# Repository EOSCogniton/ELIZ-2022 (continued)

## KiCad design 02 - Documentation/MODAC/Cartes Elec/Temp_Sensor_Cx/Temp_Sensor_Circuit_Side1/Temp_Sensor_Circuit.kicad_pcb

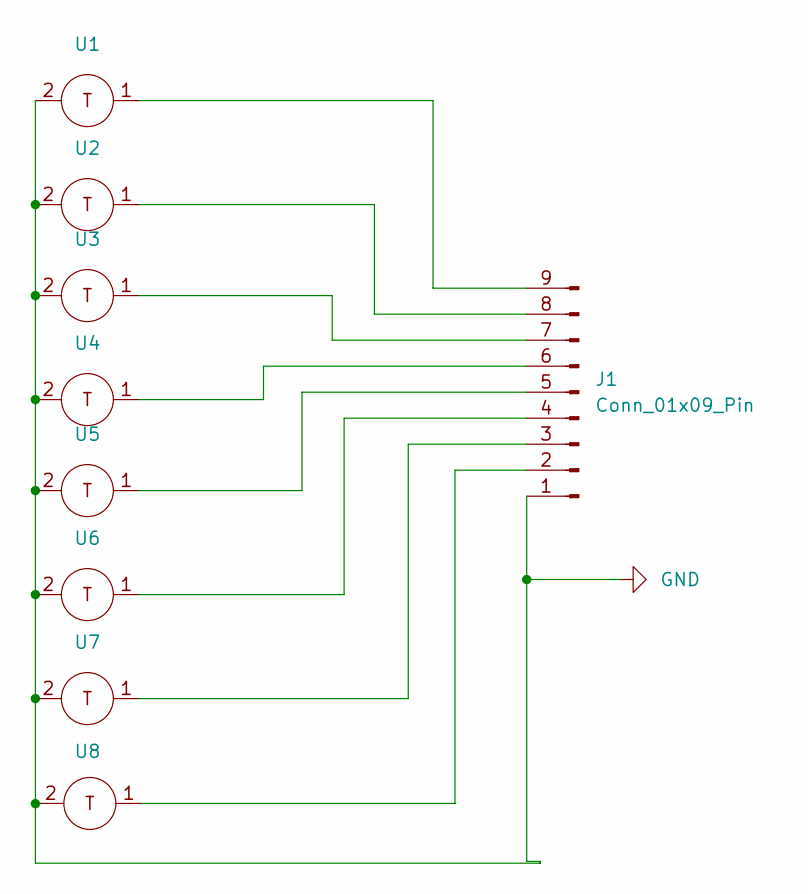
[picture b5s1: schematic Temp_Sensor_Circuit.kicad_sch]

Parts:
J1: Conn_01x09_Pin; PinHeader_1x09_P2.54mm_Vertical_SMD_Pin1Left
U1, U2, U3, U4, U5, U6, U7, U8: thermistor

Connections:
GND: J1.1, U1.2, U2.2, U3.2, U4.2, U5.2, U6.2, U7.2, U8.2
unnamed: J1.2, U8.1
unnamed: J1.3, U7.1
unnamed: J1.4, U6.1
unnamed: J1.5, U5.1
unnamed: J1.6, U4.1
unnamed: J1.7, U3.1
unnamed: J1.8, U2.1
unnamed: J1.9, U1.1

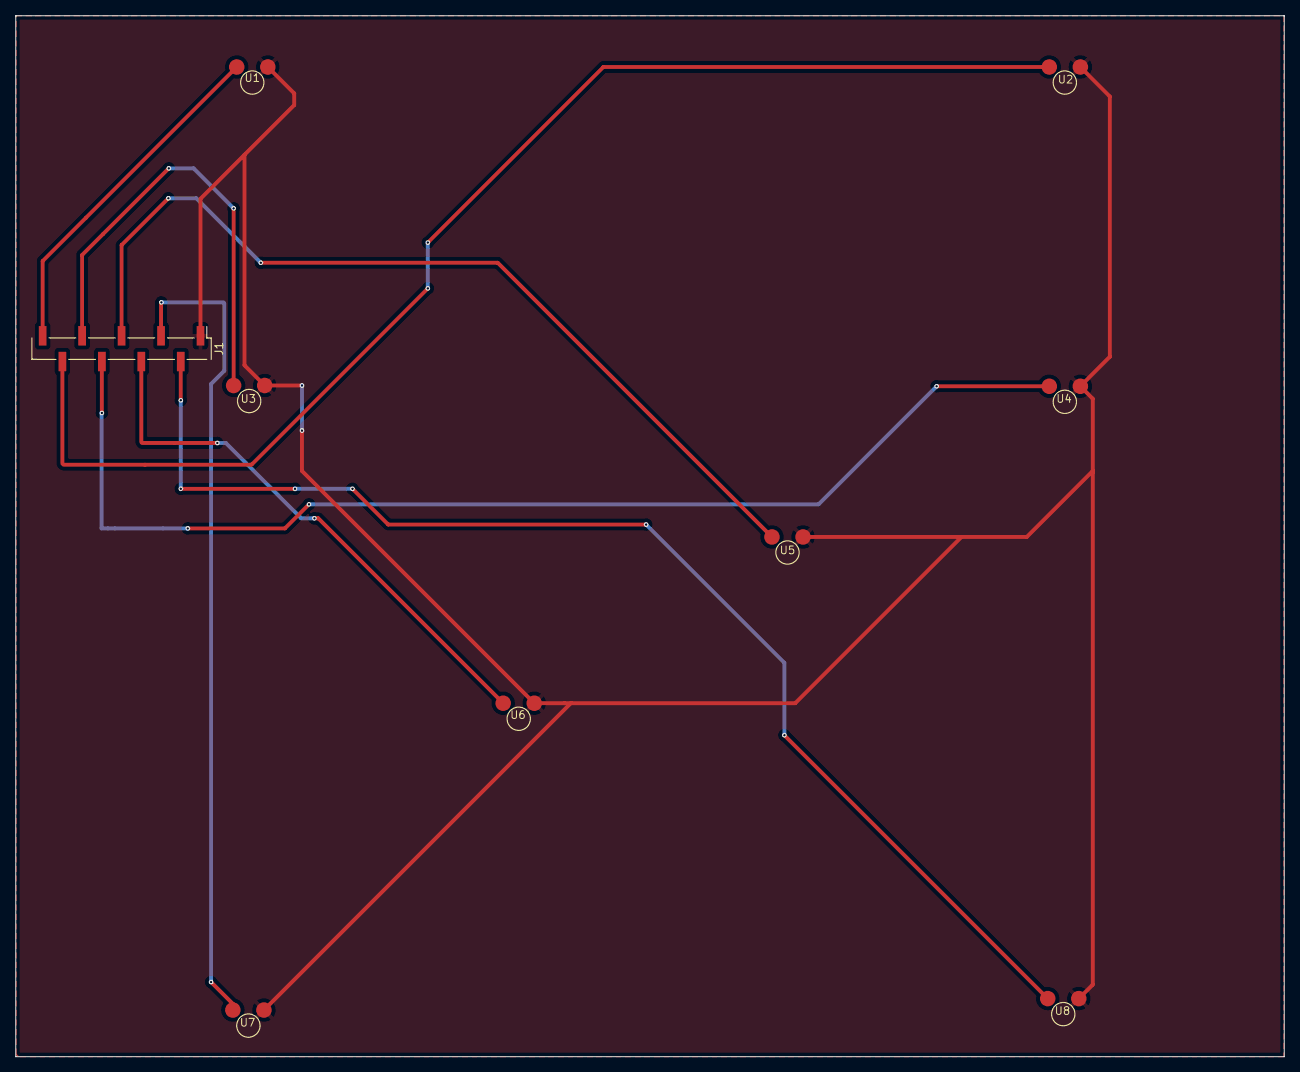
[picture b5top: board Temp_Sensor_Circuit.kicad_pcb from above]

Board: 2 copper layers, 163.3 x 134.0 mm, 9 parts (0 on the bottom side), 9 nets.

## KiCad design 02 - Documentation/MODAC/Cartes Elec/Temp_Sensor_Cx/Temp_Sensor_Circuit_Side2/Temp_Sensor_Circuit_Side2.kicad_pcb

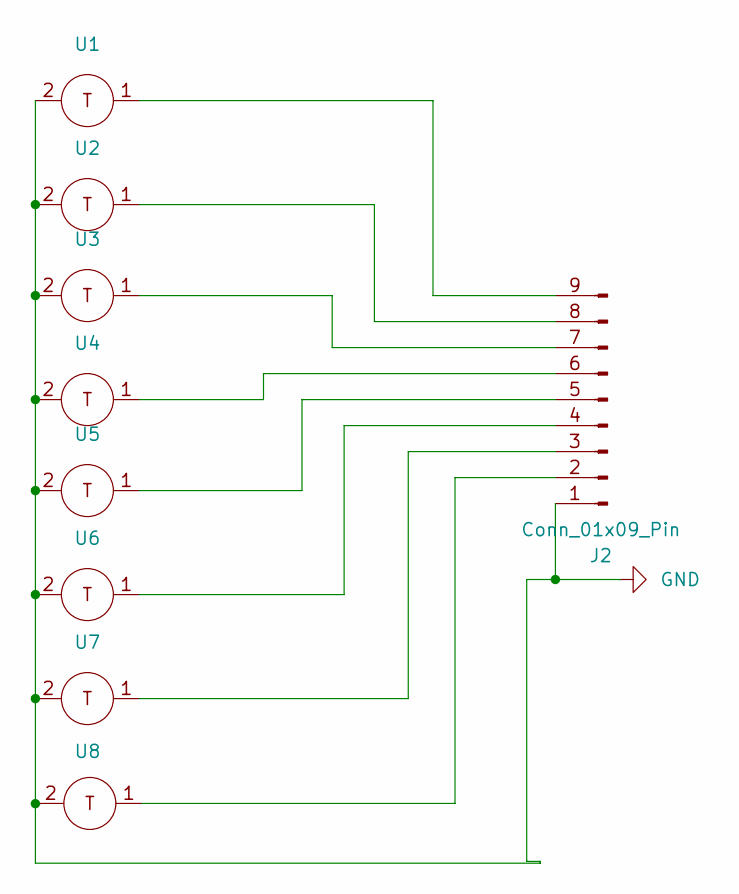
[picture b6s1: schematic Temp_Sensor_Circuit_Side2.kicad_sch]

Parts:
J2: Conn_01x09_Pin; PinHeader_1x09_P2.54mm_Vertical_SMD_Pin1Left
U1, U2, U3, U4, U5, U6, U7, U8: therm

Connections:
GND: J2.1, U1.2, U2.2, U3.2, U4.2, U5.2, U6.2, U7.2, U8.2
unnamed: J2.2, U8.1
unnamed: J2.3, U7.1
unnamed: J2.4, U6.1
unnamed: J2.5, U5.1
unnamed: J2.6, U4.1
unnamed: J2.7, U3.1
unnamed: J2.8, U2.1
unnamed: J2.9, U1.1

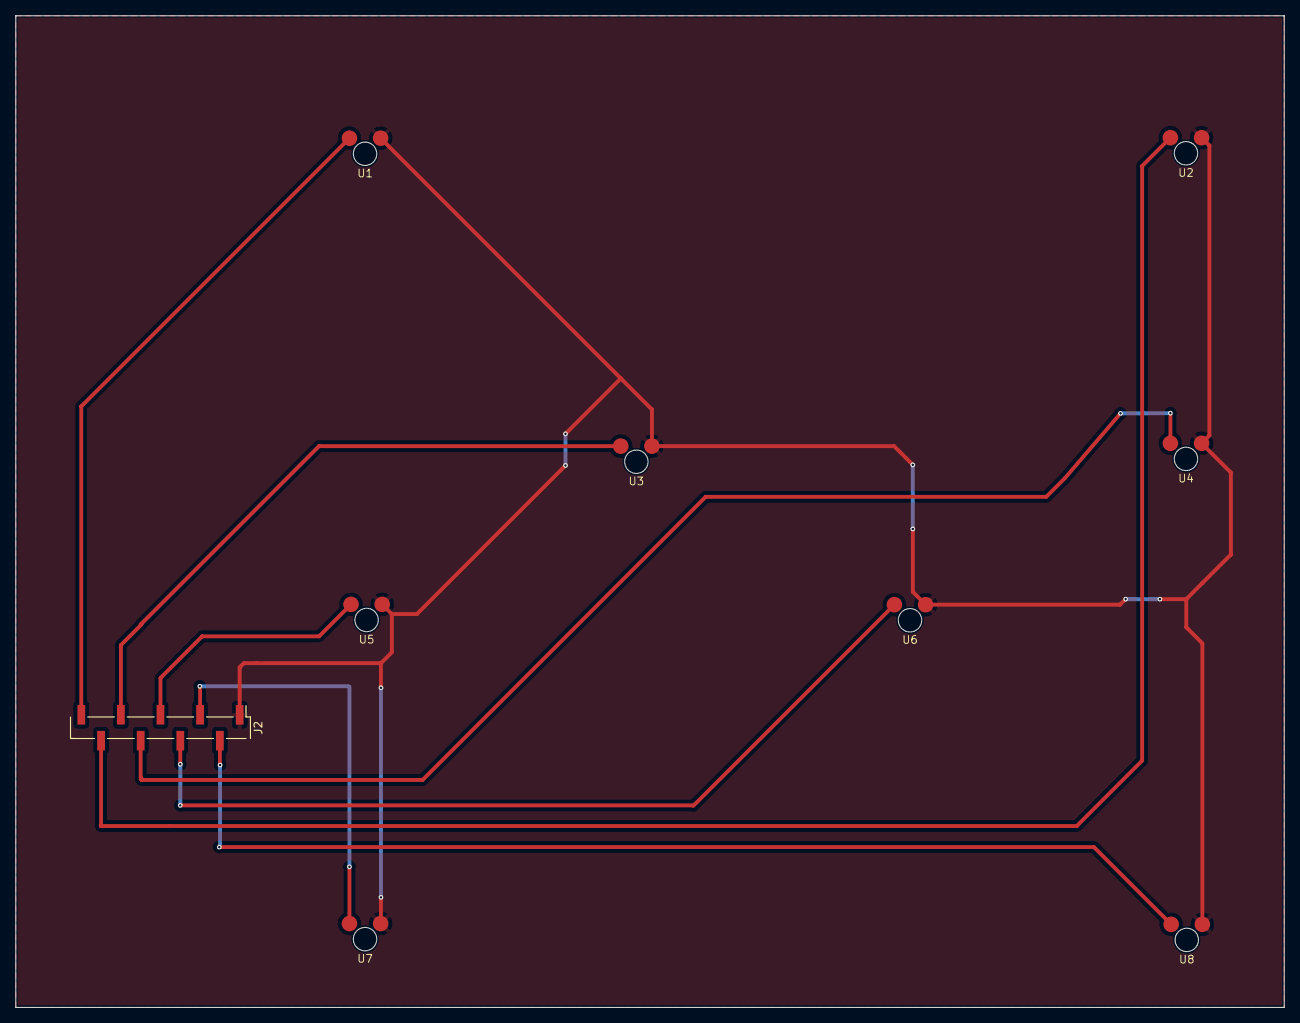
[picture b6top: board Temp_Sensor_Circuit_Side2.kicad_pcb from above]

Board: 2 copper layers, 162.7 x 127.2 mm, 9 parts (0 on the bottom side), 9 nets.

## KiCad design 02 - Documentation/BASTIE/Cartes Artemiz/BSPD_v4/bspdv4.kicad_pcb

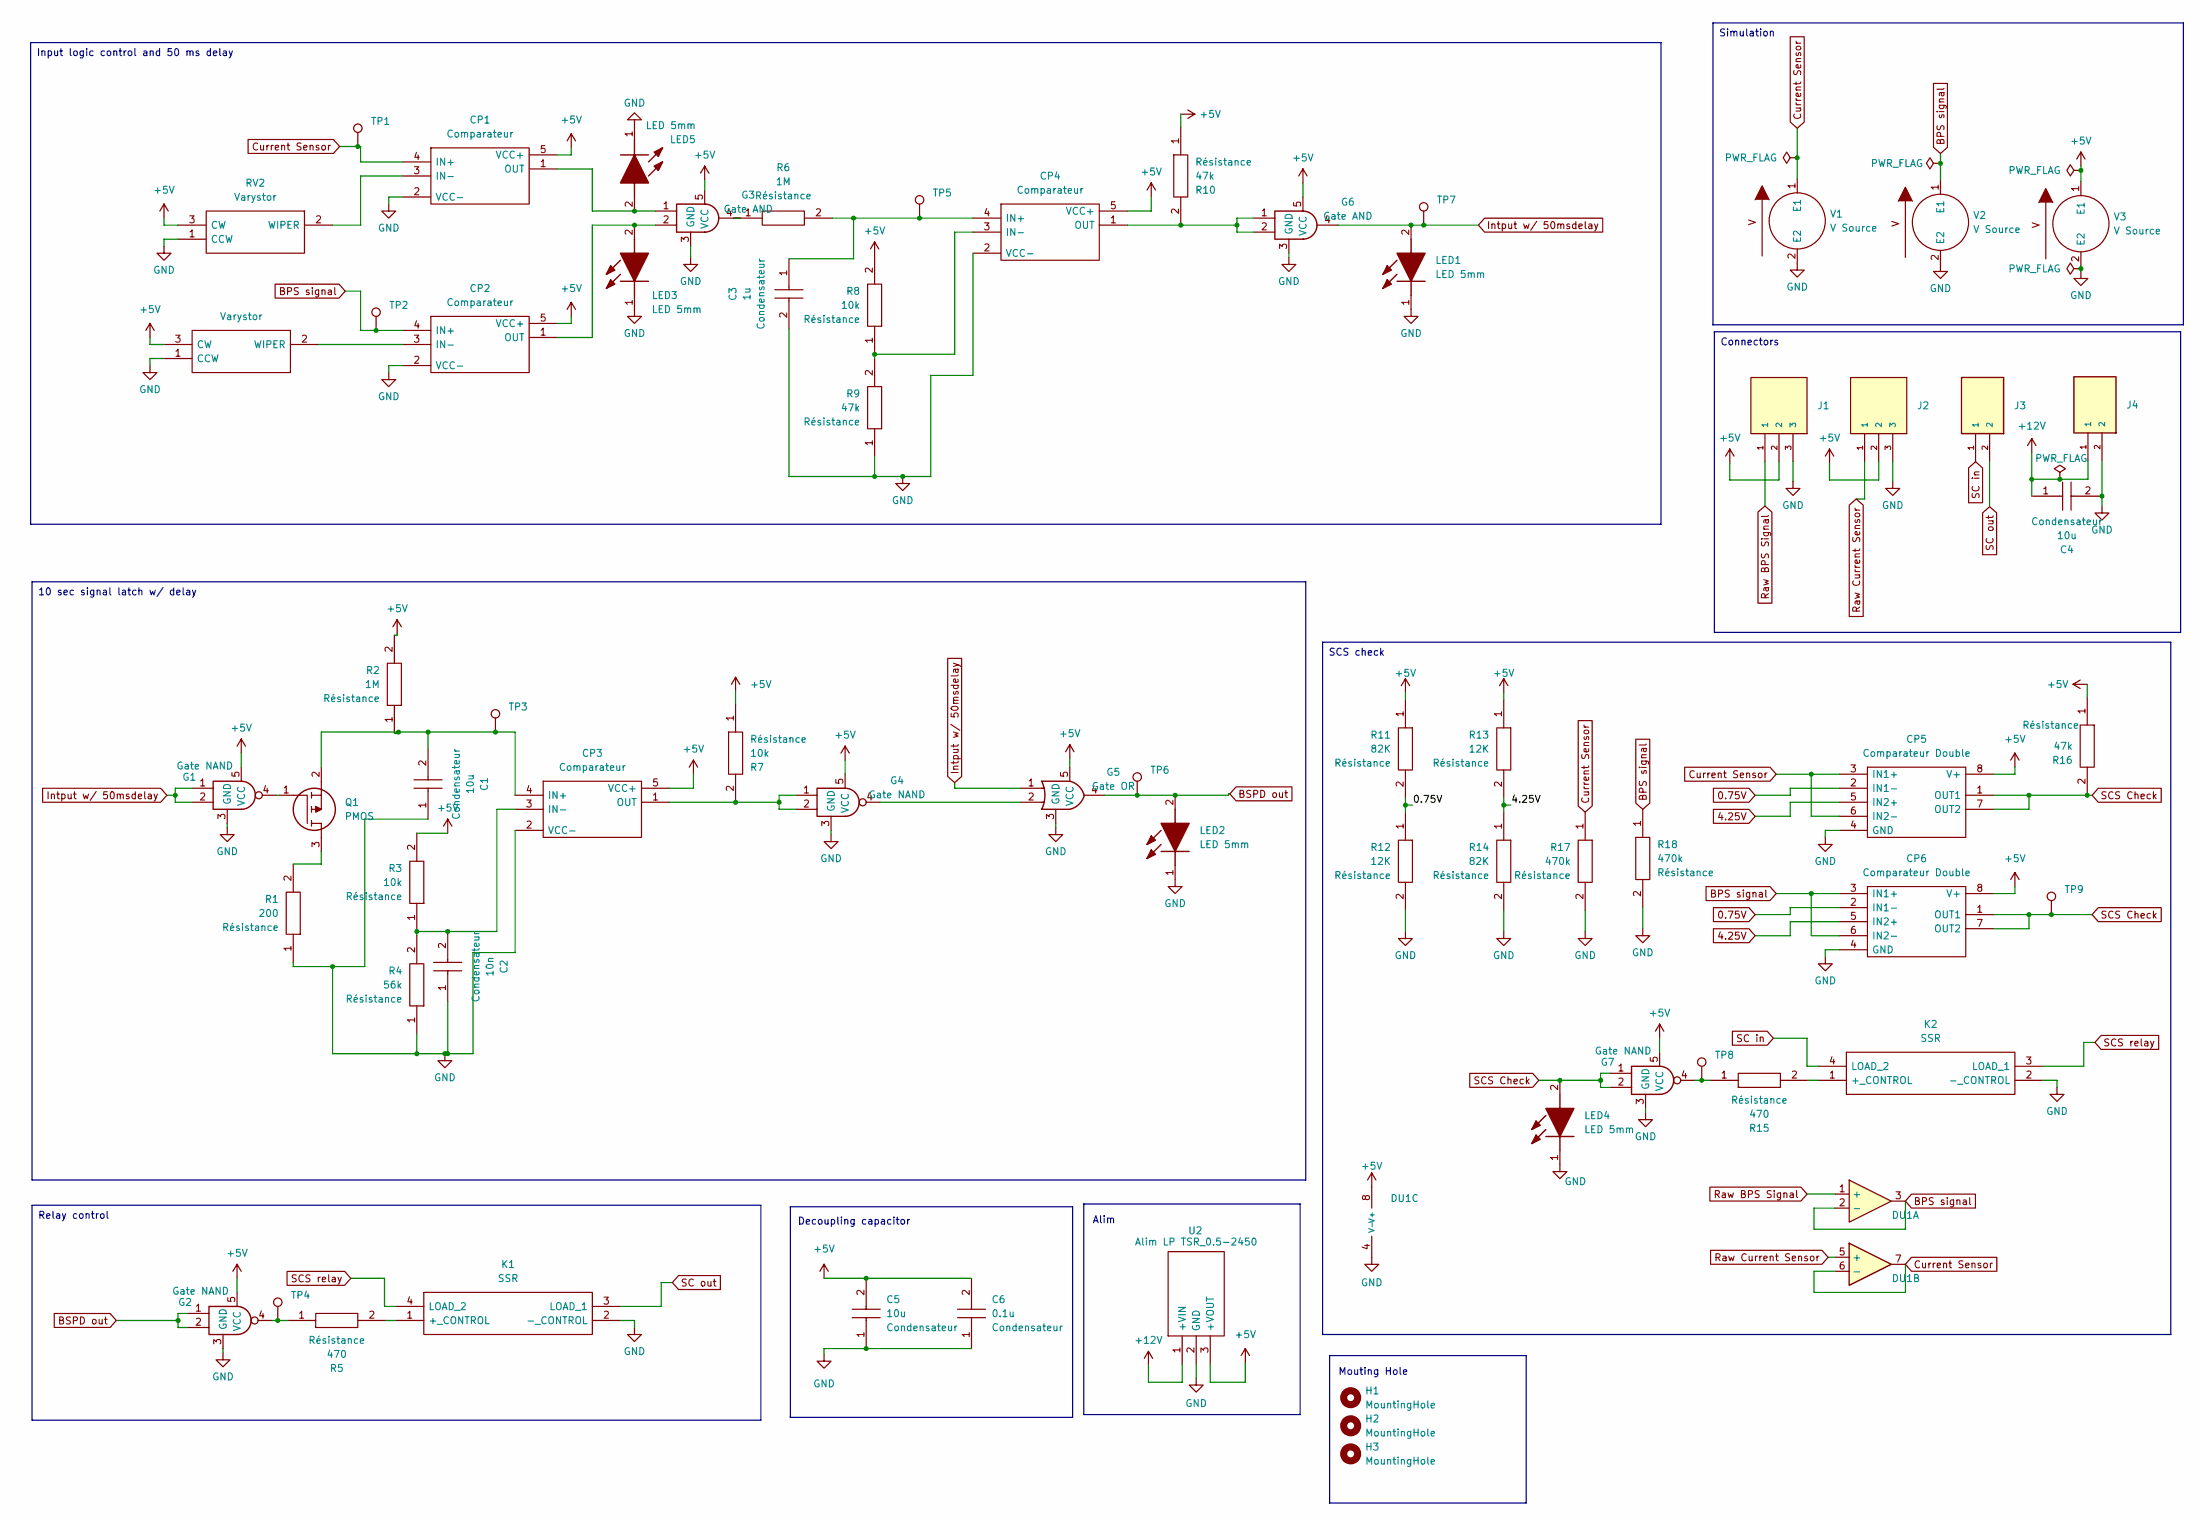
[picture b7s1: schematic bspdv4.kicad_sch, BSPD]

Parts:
C1, C4, C5: 10u; CP_Radial_D5.0mm_P2.00mm; Manufacturer_Part_Number 0805Y1000104JXT
C2: 10n; CAPC2012X130N; Manufacturer_Part_Number 0805Y1000104JXT
C3: 1u; CAPC2012X130N; Manufacturer_Part_Number 0805Y1000104JXT
C6: 0.1u; CAPC2012X130N; Manufacturer_Part_Number 0805Y1000104JXT
CP1, CP2, CP3, CP4: Comparateur TS391ILT; SOT95P280X145-5N; Manufacturer_Part_Number TS391ILT; Mouser Part Number 511-TS391IL
CP5, CP6: Comparateur Double LM393LVDR; SOIC127P600X175-8N; Manufacturer_Part_Number LM393LVDR; Mouser Part Number 595-LM393LVDR
DU1: Opamp_Dual; TSSOP-8_4.4x3mm_P0.65mm; Manufacturer_Part_Number TLV9062QPWRQ1; Mouser Part Number 595-TLV9062QPWRQ1
G1, G2, G4, G7: Gate NAND SN74AHCT1G00DBVR; SOT95P280X145-5N; Manufacturer_Part_Number SN74AHCT1G00DBVR; Mouser Part Number 595-SN74AHCT1G00DBVR
G3, G6: Gate AND SN74AHCT1G08DBVR; SOT95P280X145-5N; Manufacturer_Part_Number SN74AHCT1G08DBVR; Mouser Part Number 595-SN74AHCT1G08DBVR
G5: Gate OR SN74AHCT1G32DBVR; SOT95P280X145-5N; Manufacturer_Part_Number SN74AHCT1G32DBVR; Mouser Part Number 595-SN74AHCT1G32DBVR
H1, H2, H3: MountingHole; MountingHole_2.7mm_M2.5
J1, J2: 3P Droit 22-11-2032; MOLEX_22-11-2032; Manufacturer_Part_Number 22-11-2032; Mouser Part Number 538-22-11-2032
J3, J4: 2P Droit 2-11-2022; MOLEX_22-11-2022; Manufacturer_Part_Number 22-11-2022; Mouser Part Number 538-22-11-2022
K1, K2: SSR CPC1394GR; CPC1394GR; Manufacturer_Part_Number CPC1394GR; Mouser Part Number 849-CPC1394GR
LED1, LED2, LED3, LED4, LED5: LED 5mm; 4302H55V; Mouser Part Number 606-4302H5-5V
Q1: PMOS SI2343CDS-T1-GE3; SOT95P237X112-3N; Manufacturer_Part_Number SI2343CDS-T1-GE3; Mouser Part Number 781-SI2343CDS-T1-GE3
R1: 200; RESC3216X70N; Manufacturer_Part_Number RK73H2BLTDD2152F; Mouser Part Number N/A
R2, R6: 1M; RESC3216X70N; Manufacturer_Part_Number RK73H2BLTDD2152F; Mouser Part Number N/A
R3, R7, R8: 10k; RESC3216X70N; Manufacturer_Part_Number RK73H2BLTDD2152F; Mouser Part Number N/A
R4: 56k; RESC3216X70N; Manufacturer_Part_Number RK73H2BLTDD2152F; Mouser Part Number N/A
R5, R15: 470; RESC3216X70N; Manufacturer_Part_Number RK73H2BLTDD2152F; Mouser Part Number N/A
R9, R10, R16: 47k; RESC3216X70N; Manufacturer_Part_Number RK73H2BLTDD2152F; Mouser Part Number N/A
R11, R14: 82K; RESC3216X70N; Manufacturer_Part_Number RK73H2BLTDD2152F; Mouser Part Number N/A
R12, R13: 12K; RESC3216X70N; Manufacturer_Part_Number RK73H2BLTDD2152F; Mouser Part Number N/A
R17, R18: 470k; RESC3216X70N; Manufacturer_Part_Number RK73H2BLTDD2152F; Mouser Part Number N/A
RV1, RV2: Varystor 3296Y-1-223LF; 3296Y1223LF; Manufacturer_Part_Number 3296Y-1-223LF; Mouser Part Number 652-3296Y-1-223LF
TP1, TP2, TP3, TP4, TP5, TP6, TP7, TP8, TP9: type="R" model="TestPoint" lib=""; TestPoint_Pad_D2.0mm
U2: Alim LP TSR_0.5-2450; TSR-0.5-2433; Manufacturer_Part_Number TSR 0.5-2450; Mouser Part Number 495-TSR0.5-2450
V1, V2, V3: 5

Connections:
0.75V: CP5.2 (IN1-), CP6.2 (IN1-), R11.2, R12.1
4.25V: CP5.5 (IN2+), CP6.5 (IN2+), R13.2, R14.1
+5V: C5.2, C6.2, CP1.5 (VCC+), CP2.5 (VCC+), CP3.5 (VCC+), CP4.5 (VCC+), CP5.8 (V+), CP6.8 (V+), DU1.8 (V+), G1.5 (VCC), G2.5 (VCC), G3.5 (VCC), G4.5 (VCC), G5.5 (VCC), G6.5 (VCC), G7.5 (VCC), J1.2, J2.2, R2.2, R3.2, R7.1, R8.2, R10.1, R11.1, R13.1, R16.1, RV1.3 (CW), RV2.3 (CW), U2.3 (+VOUT), V3.1 (E1)
+12V: C4.1, J4.1, U2.1 (+VIN)
BPS signal: CP2.4 (IN+), CP6.3 (IN1+), CP6.6 (IN2-), DU1.2 (-), DU1.3, R18.1, TP2.1, V2.1 (E1)
BSPD out: G2.1, G2.2, G5.4, LED2.2 (A), TP6.1
Current Sensor: CP1.4 (IN+), CP5.3 (IN1+), CP5.6 (IN2-), DU1.6 (-), DU1.7, R17.1, TP1.1, V1.1 (E1)
GND: C1.1, C2.1, C3.2, C4.2, C5.1, C6.1, CP1.2 (VCC-), CP2.2 (VCC-), CP3.2 (VCC-), CP4.2 (VCC-), CP5.4 (GND), CP6.4 (GND), DU1.4 (V-), G1.3 (GND), G2.3 (GND), G3.3 (GND), G4.3 (GND), G5.3 (GND), G6.3 (GND), G7.3 (GND), J1.3, J2.3, J4.2, K1.2 (-_CONTROL), K2.2 (-_CONTROL), LED1.1 (K), LED2.1 (K), LED3.1 (K), LED4.1 (K), LED5.1 (K), R1.1, R4.1, R9.1, R12.2, R14.2, R17.2, R18.2, RV1.1 (CCW), RV2.1 (CCW), U2.2 (GND), V1.2 (E2), V2.2 (E2), V3.2 (E2)
Intput w/ 50msdelay: G1.1, G1.2, G5.1, G6.4, LED1.2 (A), TP7.1
unnamed: CP1.3 (IN-), RV2.2 (WIPER)
unnamed: CP1.1 (OUT), G3.1, LED5.2 (A)
unnamed: CP2.3 (IN-), RV1.2 (WIPER)
unnamed: CP2.1 (OUT), G3.2, LED3.2 (A)
unnamed: C1.2, CP3.4 (IN+), Q1.2, R2.1, TP3.1
unnamed: C2.2, CP3.3 (IN-), R3.1, R4.2
unnamed: CP3.1 (OUT), G4.1, G4.2, R7.2
unnamed: C3.1, CP4.4 (IN+), R6.2, TP5.1
unnamed: CP4.3 (IN-), R8.1, R9.2
unnamed: CP4.1 (OUT), G6.1, G6.2, R10.2
unnamed: G1.4, Q1.1
unnamed: G2.4, R5.1, TP4.1
unnamed: G3.4, R6.1
unnamed: G4.4, G5.2
unnamed: G7.4, R15.1, TP8.1
unnamed: K1.1 (+_CONTROL), R5.2
unnamed: K2.1 (+_CONTROL), R15.2
unnamed: Q1.3, R1.2
Raw BPS Signal: DU1.1 (+), J1.1
Raw Current Sensor: DU1.5 (+), J2.1
SC in: J3.1, K2.4 (LOAD_2)
SC out: J3.2, K1.3 (LOAD_1)
SCS Check: CP5.1 (OUT1), CP5.7 (OUT2), CP6.1 (OUT1), CP6.7 (OUT2), G7.1, G7.2, LED4.2 (A), R16.2, TP9.1
SCS relay: K1.4 (LOAD_2), K2.3 (LOAD_1)

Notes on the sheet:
Relay control
10 sec signal latch w/ delay
Connectors
SCS check
Simulation
Input logic control and 50 ms delay
Alim
Mouting Hole
Decoupling capacitor

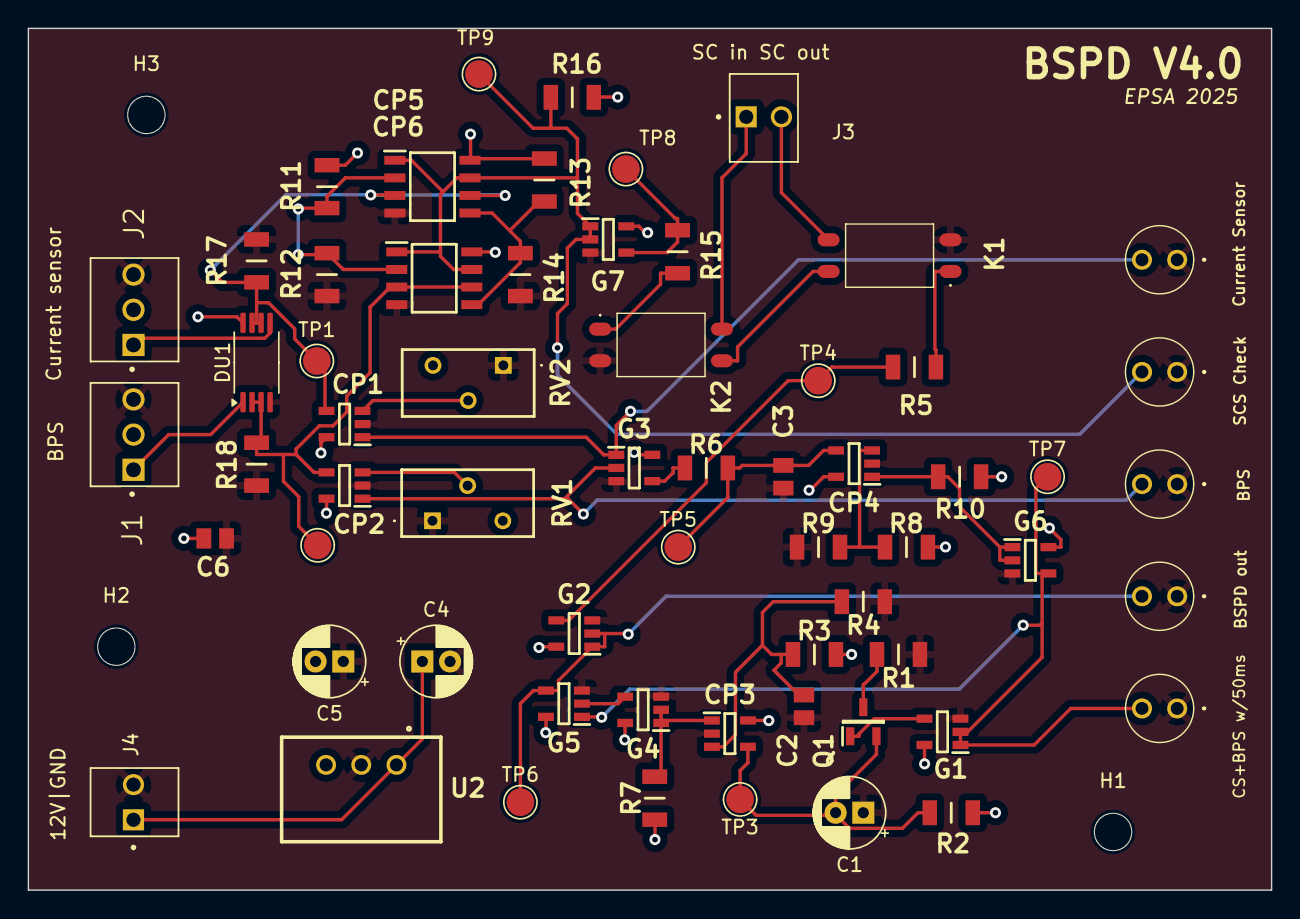
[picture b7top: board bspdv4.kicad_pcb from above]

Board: 2 copper layers, 89.8 x 62.2 mm, 65 parts (0 on the bottom side), 33 nets.

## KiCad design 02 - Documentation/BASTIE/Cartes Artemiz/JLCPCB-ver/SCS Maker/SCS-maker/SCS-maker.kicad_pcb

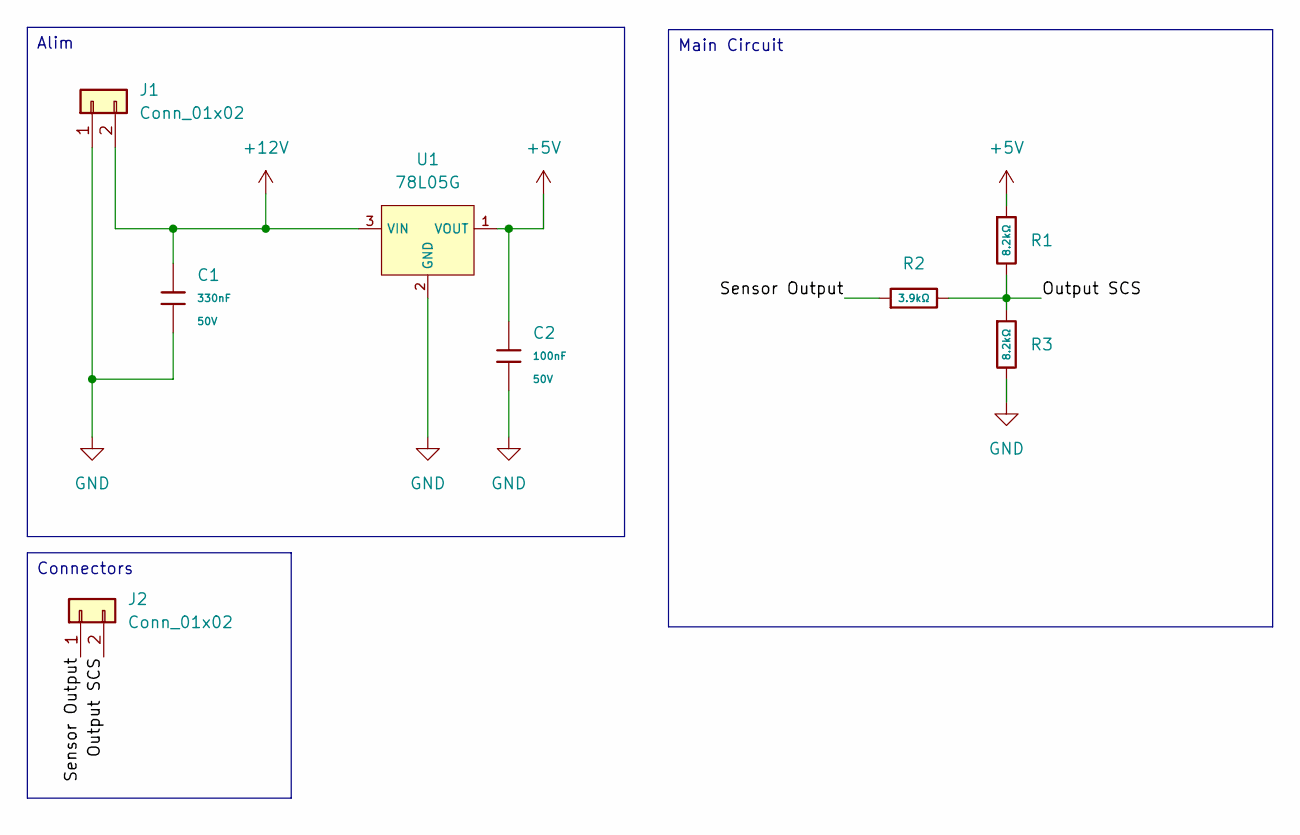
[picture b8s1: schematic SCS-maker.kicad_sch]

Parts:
C1: 330nF; C_0805; Voltage Rated 50V; Tolerance ±10%; Part 0805B334K500NT; LCSC C1740
C2: 100nF; C_0805; Voltage Rated 50V; Tolerance ±10%; Part CC0805KRX7R9BB104; LCSC C49678
J1, J2: Conn_01x02; Molex_KK-254_AE-6410-02A_1x02_P2.54mm_Vertical
R1, R3: 8.2kΩ; R_0805; Overload Voltage (Max) 150V; Tolerance ±1%; Part 0805W8F8201T5E; LCSC C17828
R2: 3.9kΩ; R_0805; Overload Voltage (Max) 150V; Tolerance ±1%; Part 0805W8F3901T5E; LCSC C17614
U1: 78L05G; SOT-89-3_L4.5-W2.5-P1.50-LS4.2-BR; Output Voltage 5V; Dropout Voltage 1.7V@(40mA); Part 78L05G-AB3-R; LCSC C71136

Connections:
+5V: C2.1, R1.1, U1.1 (VOUT)
+12V: C1.1, J1.2, U1.3 (VIN)
/Output SCS: J2.2, R1.2, R2.2, R3.1
/Sensor Output: J2.1, R2.1
GND: C1.2, C2.2, J1.1, R3.2, U1.2 (GND)

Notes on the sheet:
Connectors
Main Circuit
Alim

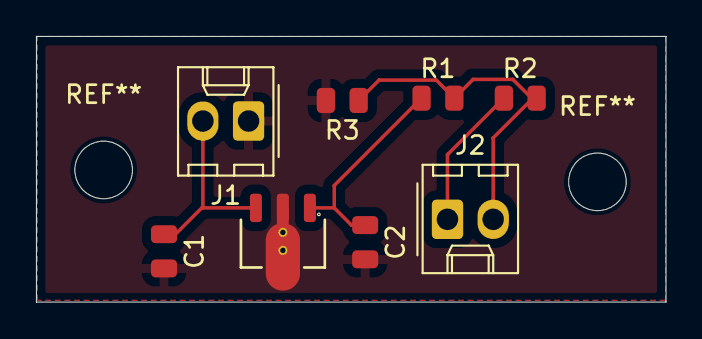
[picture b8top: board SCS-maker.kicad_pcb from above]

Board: 2 copper layers, 35.0 x 14.8 mm, 8 parts (0 on the bottom side), 5 nets.

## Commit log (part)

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2024-04-03 gabarit dessous tsbox rectification
2024-04-03 tsbox
2024-04-03 Maquettage TSAC
2024-04-04 BSPD valky
2024-04-05 Création gabarit pushclip 1
    Création gabarit pushclip 1
2024-04-05 coins arrondis
    coins arrondis
2024-04-05 MEP gabarits pushclip
    MEP gabarits pushclip
2024-04-14 push pour José
2024-04-15 Modifications cartes
    Prise en compte des retours ECT + PCBs
2024-04-17 Vérification PCBs + Fichiers Fabrication
    Préparation pour production des PCBs
2024-04-17 Maquettage assemblage batterie (1/?)
    Ajout des rails sur le TSAC
    Corrections de certaines dimensions
    Ajout d'une première chape
2024-04-19 IAD v2 (1/?)
2024-04-19 Maquettage assemblage batterie (2/?)
    Beaucoup de filaires, quelques équipements
2024-04-20 Dossiers au bon endroit
2024-04-20 Maquettage assemblage batterie (3/?)
    Maquettage du point d'attache arrière bas
    Filaire pour les attaches avant
2024-04-21 Maquettage assemblage batterie (5/?)
    Maquettage attaches avant
2024-04-21 Maquettage assemblage batterie (6/?)
    Fin du maquettage des équipements v1
2024-04-22 gabarit overflow bottle et catchcan
2024-04-23 Déplacements sous MODAC
2024-04-23 Maquettage assemblage batterie (7/?)) + MEPs (2/2=
    Ajout de pièces en doublon car ne passant pas en MEPs (non résolu)
    Fin des MEPs et compression en .zip
2024-04-24 maquette IAD sur FR
2024-04-24 (2/2)
2024-04-24 Datasheet colle
2024-04-24 gabarit radia
2024-04-24 Maquettage module et TSAC (1/?)
    Modélisation du CTMD
    Ajout des dossiers correspondants
2024-04-25 Test Git formation
2024-04-25 Test Git encore encore
2024-04-26 Maquettage TSAC (1/?)
    Ajout des premiers volumes et parois
2024-04-27 Maquettage module (1/?)
    Ajout des busbars
    Connectique HV
2024-04-30 Auto stash before rebase of "master" onto "origin/master"
2024-04-30 Maquettage batterie en vrac
    Modules, CTMD et assy
2024-04-30 Maquettage chapes moteur
    Deuxième couche par rapport à Carlos
    Corrections sur les chapes U0 Right (PDV pilote) sur la coaxialité
    Vérification des différentes positions
2024-05-03 Maquettage fixations batterie (8/?)
    Ajout des symétries des fixations.
2024-05-03 Gabarit baquet (1/?)
    Pas terminé du tout
2024-05-04 Gabarit batterie (2/?)
2024-05-04 Gabarit batterie (3/?)
    Ajout de poches pour le tube penché
    Ajout d'une plaque par utilisation de références externes
2024-05-05 Gabarit batterie (5/?)
    Ajout de nouvelles plaques
2024-05-05 Gabarit Batterie (6/?)
    Symétrie + nom fichier
2024-05-06 Gabarit batterie (8/?)
    Nouvelle plaque
2024-05-06 Gabarit batterie (9/?)
2024-05-07 gabarit CHAIPE convertion dxf to svg
2024-05-07 Modifs gabarit pushclips
2024-05-07 Gabarit batterie (10/?)
    Correction de l'épaisseur des fentes de toutes les pièces
2024-05-09 gabarit encore
2024-05-12 Gabarit batterie (12/?)
    Supports de tubes
    Ajout de supports transversaux
    Ajout de fentes
2024-05-13 Gabarit moteur
2024-05-13 Gabarit Baquet arrière
    MEP
2024-05-14 Maquettage Firewall
    Premiers test
2024-05-14 Pare-feu
    début de pare-feu (douteux)
2024-05-15 pare-feu
    début maquettage chapes
2024-05-15 Encore pare-feu
2024-05-15 gabarit chaipe tsbox part1
2024-05-15 gabarit chaipe part 2 (enfin !)
2024-05-16 pare-feu
    c'est douteux mais ça prend forme
2024-05-16 Import module ECT
2024-05-17 Ajout busbar module
2024-05-17 Documentation IAD v2
2024-05-17 Ajout des deux versions de l'IAD, v1 et v2
2024-05-18 fin side firewall
2024-05-19 modifs mineures chape EN
2024-05-20 st_05001 mep
2024-05-21 Add AMS_IMD reset chargeur
2024-05-22 modifs mineures
2024-05-22 BSPD folder update
2024-05-22 VC bis Led rounded corner + DRC ok
2024-05-22 Correction SCS Maker
2024-05-22 Correction DSB
2024-05-22 MEP chainfield
2024-05-22 MEP LAs et rajout ancienne firewall
2024-05-22 Push Firewall
    Rename des chapes
    Correction de la side plate
2024-05-22 MEP perçage TSBox
2024-05-22 MEP Chapes firewall
2024-05-22 Maquettage Firewall
    Redécoupe de la plaque latérale
    Correction MS_04005
2024-05-22 Symétrie plaque latérale firewall
2024-05-23 Modification MEP MS_04005
2024-05-23 Maquettage encore
    Chape coudée pour la FireWall
    Ajout de certaines plaques
2024-05-23 MEP MS_04004 Bracket 3
    Correction MEP chape coudée Firewall
2024-05-23 Rajout fichier igs dans 5eme vague
2024-05-24 Fin module sans tenue mécanique
2024-05-25 Test Steering System
2024-05-27 Correction gabarit blocage sangles harnais
2024-05-27 Correction chapes LAS 2/2
    Triangle arrière done aussi
2024-05-28 Ajout MEP gabarits moteur
2024-05-28 Modif écartement chapes Tie Rod
2024-05-30 MEPs EDR
    Top Vue
    Side Vue
    Front Vue
    3D
2024-06-02 Oupsi d oupsi resistance de tirage
2024-06-02 Léger correctif logique TSAL
2024-06-03 Module et Circuit LV Batterie HV
2024-06-05 Ajout compo convertisseur 600V + IMD SCS + BOM AIR
2024-06-05 LED right direction
2024-06-06 Déplacements cartes elec Batterie vers MODAC
2024-06-07 Routage AMS
2024-06-08 MAJ modèles 3D KICAD
2024-06-10 Légère modif pistes AMS dongle
2024-06-10 Renommage pour plus de clareté
2024-06-14 Prise en compte retours JDL
2024-06-14 Modifs légères BMS/AMS
2024-06-16 Update cirly files
2024-06-16 Update SCS LEDs schematic
    For T11.9.6 compliance
2024-06-17 Gerbers cartes modac
2024-06-20 Le module il est carré.
    Et oui
2024-06-23 PCBs + fichiers de fabrication
    Update SCS LEDs et retours TSAL ESF
2024-06-27 ajout quelques composants
2024-06-27 légères modifs bms
2024-06-27 MAJ module 3D
2024-06-30 Import step + modif tsac
2024-07-01 SES v2 attaches batterie
    Premiers schémas pour le SES, partie sur les fixations de l'accumulateur
2024-07-02 Test CTMD
2024-07-02 SES v2 et SE3D v2
    SE3D actualisé avec les nouvelles attaches, compressé en 7z et mis sur le site du FSG
    Partie fixations de la batterie du SES complétée : positions, calculs de résistance des équipements et des vis dans les différents cas de charge
2024-07-03 Import step to catproduct batterie
2024-07-04 Grosse update maquette batterie
2024-07-05 Quasi fin modele 3D batterie + modif TSAC Voltage
2024-07-09 update prod carte modac
2024-07-12 Modif accumulator
2024-07-16 Fin TSAC + Correction schema LV batterie
2024-07-16 Modifs batterie
2024-07-26 Modif CAN AMS.dongle
2024-09-03 Modifs AMS Dongle + gerbers
2024-09-04 Update schematique chargeur
2024-09-06 Debut MEP batterie
2024-09-07 Gabarits de SU_14011 et ST_04003
2024-09-10 Maj plan batterie + Refonte supports relais
2024-09-17 Gros rework batterie + cartes batterie part1
2024-09-18 Fin drafting Inside Container
2024-09-19 Update fixation batterie
2024-09-20 Nettoyage fixation batterie
2024-09-24 Modif Discharge controller
2024-09-24 Fin revert commit
2024-09-26 Plans Isymeca
2024-09-26 Gerbers MODAC
2024-09-30 Premières corrections gabarit susp arrière
2024-09-30 MAJ Gerber Modac
2024-10-01 gabarit GA_ST04003 partie 1
2024-10-03 Gabarit ST et chapes moteur
2024-10-05 Modifications FireWall MS_A400
    Contient une modification du fichier Frame pour publication de certains éléments
2024-10-09 nouveau boitier TSBox (pour usiner)
2024-10-10 Correction PCB AMS et autres
2024-10-10 correct opamp tsal
2024-10-12 MEP chapes LAS pour la mache
2024-10-13 Dernières MEP la mache
2024-10-14 Symétrie des chapes MS_A400
2024-10-14 Ajout des derniers fichiers MS_A400
2024-10-15 Gabarit tableau de bord middle
2024-10-17 Reprise du gabarit suspension arrière (1/?)
2024-10-19 Dessin gabarits FL_Damper et FRocker
2024-10-20 Gabarits ST_05001/ST_05002 + bcp de MEP
2024-10-22 Réparation des ficheirs CATIA
2024-10-22 Réparation des fichiers CATIA
2024-10-22 fichier prod cartes cirly
2024-10-23 Créer le fichier bonjour
    ..
2024-11-04 Début gabarits triangle arrière
2024-11-04 gabarit triangle arriere haut
2024-11-06 BMS Testboard
2024-11-11 gabarit_triangle_arriere_bas
2024-11-18 MEPs gabarit batterie
2024-11-20 Gabarit tableau de bord
2024-12-01 BMS 18 Channel V1
2024-12-03 Ajout Application Banc
2024-12-12 Rangement fichiers banc + carte controle banc
2024-12-14 BMS 18 modif
2024-12-15 gabarit steering shaft
2024-12-17 MEP Gabarit ST
2025-01-29 Ajout et modifs BMS 18 footprint
2025-01-30 Basculeurs arrière V2
    Fin de modif des chapes et mise à jour du gabarit
2025-01-30 MEP Frame brake
2025-02-04 TSboX + inverter
2025-02-04 TSbox fini
2025-02-13 Modif TSAC
2025-02-15 BMS 13 0 erreur
2025-02-16 Update carte controle banc + maj fs rules
2025-02-17 bien_relié
2025-02-18 Support moteur v2
2025-02-19 Encore des modifs du support moteur
2025-02-26 modifs tsac
2025-02-27 BOMs et BMS Testboard
2025-03-04 BMS Testboard PCB finito
2025-03-06 Support moteur (fin)
    Modifs support + MEP pour envoi en prod
2025-03-10 Controle banc via CAN
2025-03-12 amelioration interface banc
2025-03-13 ASES et Docs prod BMS13
2025-03-13 Update ASES
2025-03-13 Documents SE3D
    quelques modifs non désirées si ce monde est bon ça ne créé pas de conflit
2025-03-13 SE3D encore
    j'ai cassé le GIT mais je crois c'est réparé là
2025-03-13 Ajout IAD et rendu visuel pour SES
2025-03-13 ASES V.10
2025-03-14 ASES 😭
2025-03-14 Ajout SES
2025-03-14 FS_SES25 v1.1
2025-03-16 Parois TSAC
2025-03-16 Update cadre_cellule_mark 3
    Automatisation du modele
2025-03-18 Rajout puzzle cadre_mark3
2025-03-18 Quelques modifs TSAC + Assemblage début
2025-03-23 Update Cadre_cellule_Mark3.CATPart
    Rajout des dentelures
2025-03-24 Couvercle TSAC
2025-03-24 Update Cadre_cellule_Mark3.CATPart
    Rajout du 3eme plug
2025-03-24 Modifs du couvercle Tsac
    Modifs du couvercle Tsac
2025-03-25 Dentelures Cadre Cellul
2025-04-01 plaque à imprimer
2025-04-13 Update BEnch
2025-04-18 Fichiers découpe Casing module
2025-04-19 Update FS25_SES_v1_EPSA.xlsx
    Ajout Chassis Pics SES
2025-04-21 SES v2
2025-04-25 VCU maj
2025-04-29 jlcpcb pcbs
2025-04-29 SES v3
    Ajout des photos attaches batterie
2025-05-12 Couvercle TSAC
    Reparation de l'esquisse
2025-05-12 TSAC remis à jour
    Debugage du couvercle TSAC
2025-05-15 TSAC couvercle modif
2025-05-18 Rajout tubes filaires
2025-05-21 corrections jlcp ver cartes
2025-05-21 Restauration version Axel de février 2025
2025-05-22 MEP chainshield
    MEP des chapes pour fixer le protège-chaine + modif et MEP du p-c
2025-05-22 casing moteur
    v1 support moteur, attention il utilise des modifs faites dans eliz-2021
2025-05-24 TsACOS
2025-05-26 TSAC Assembly et TSAC Mark II modif
2025-05-26 TsACOS elargissement et Assembly
2025-05-28 ajout dxf
    toujours les casing
2025-05-28 Modification du connecteur et des pads
2025-05-28 SES v5 modif
2025-05-29 modif ses v5
2025-06-02 pcb_therm
2025-06-04 Modif section nouveau tube
2025-06-04 Nouveaux inserts direction
2025-06-04 SES v6
2025-06-06 Auto stash before rebase of "master" onto "origin/master"
    MEP TSAC
2025-06-06 Ajout CRD
2025-06-06 Ajout fichier .stp
2025-06-07 BSPD v4
2025-06-09 AMS IMD Reset v3
2025-06-11 Ajouts habilitations elec
2025-06-11 Ajout symétrie tube harnais
2025-06-11 MEP TSAC et tubes harnais
    MEP TSAC finito et les tubes supplémentaires sont exportés en .stp vamos
2025-06-13 BSPD v4 / AMS IMD v3
2025-06-16 MEP Inserts
    Nouveaux inserts prêts ouais
2025-06-25 MEP Casing module
    MEP de la v2, manque le truc bizarre sur le dessus @salim
2025-06-25 MAJ cartes électroniques
2025-06-25 Truc bizarre sur le dessus commencé @Martin
2025-07-03 Nouveau casing module
    C'est la fête le nouveau casing est arrivé (manque juste la fixation du connecteur HV), attention c'est du lourd
2025-07-08 MAJ Modules
    J'ai collé à l'envers mais c'est pas grave normalement
2025-07-17 Mise a jour BMS
2025-07-18 Batterie et catia
    début modifs batterie et ajout tutos catia
2025-07-22 Ajout DXF
2025-07-23 TSAC et modules
    Nouvel agencement TSAC et nouvelle version modules pour FR-4
2025-07-23 Trous modules
    j'avais oublié les trous
2025-07-24 update dxf
    encore des trucs
2025-07-24 Modif BMS_VF, changement AOP
2025-07-24 Changement texte V BMS
2025-08-05 Design support
    Ajout design support pour FSS
2025-08-08 Tuto dim batterie
2025-10-21 moteur roue pédagogique
